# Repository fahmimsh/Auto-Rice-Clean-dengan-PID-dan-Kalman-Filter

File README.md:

# Auto-Rice-Clean-dengan-PID-dan-Kalman-Filter

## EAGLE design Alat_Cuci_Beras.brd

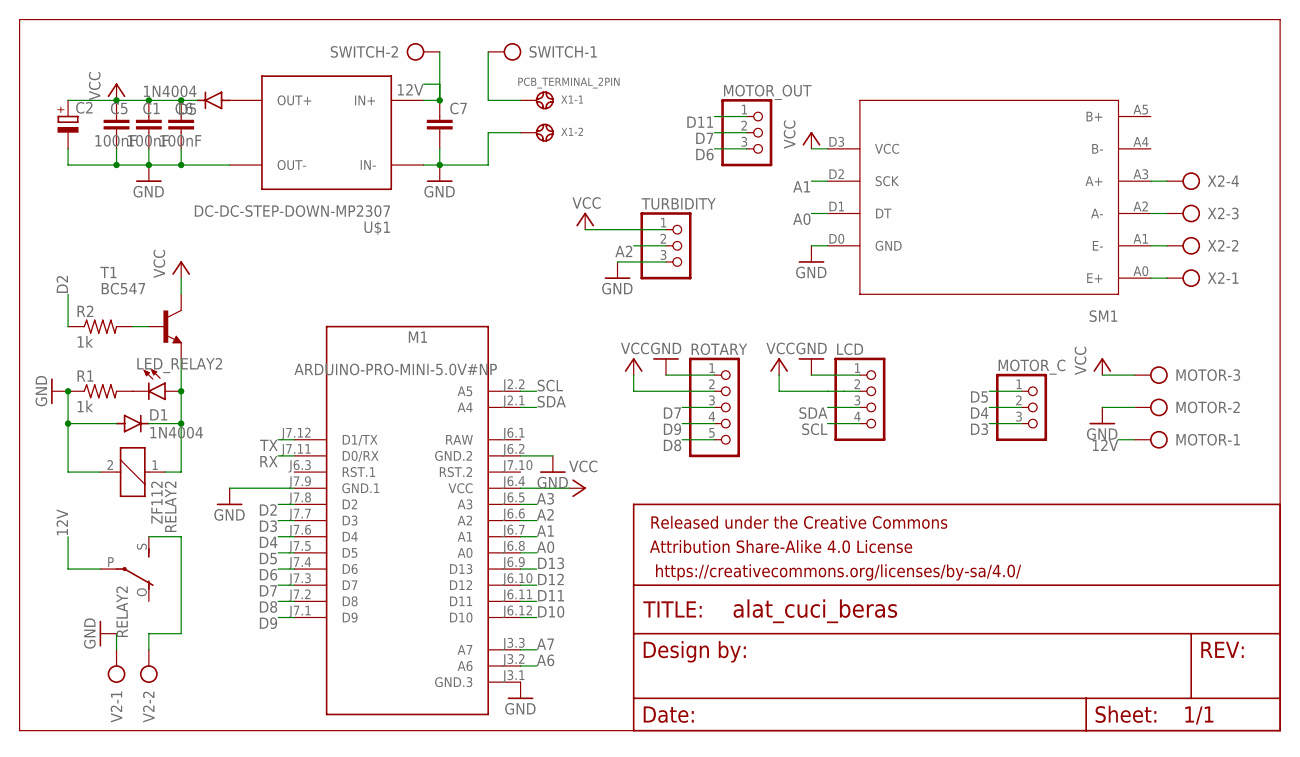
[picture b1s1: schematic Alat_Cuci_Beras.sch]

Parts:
C1, C5, C6: 100nF; C0805K
C2: CPOL-EUE2.5-6; E2,5-6
C7: C-EU050-030X075; C050-030X075
D1, D5: 1N4004; DO41-10
FRAME1: FRAME-LETTER; CREATIVE_COMMONS
LCD: PINHD-1X4; 1X04
LED_RELAY2: LED3MM; LED_3MM
M1: ARDUINO-PRO-MINI-5.0V#NP; ARDUINO-PRO-MINI#NP
MOTOR: AK500/3
MOTOR_C: PINHD-1X3; 1X03
MOTOR_OUT: PINHD-1X3; 1X03
R1: 1k; R0805
R2: 1k; 0207/10
RELAY2: ZF112
ROTARY: PINHD-1X5; 1X05
SM1: HX711
SWITCH: AK500/2
T1: BC547; TO92
TURBIDITY: PINHD-1X3; 1X03
U$1: DC-DC-STEP-DOWN-MP2307
V2: AK500/2
X1: PCB_TERMINAL_2PIN
X2: AK500/4

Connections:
12V: C7.1, MOTOR.1, RELAY2.P, SWITCH.2, U$1.IN+
A0: M1.J6.8 (A0), SM1.D1 (DT)
A1: M1.J6.7 (A1), SM1.D2 (SCK)
A2: M1.J6.6 (A2), TURBIDITY.2
A3: M1.J6.5 (A3)
A6: M1.J3.2 (A6)
A7: M1.J3.3 (A7)
D2: M1.J7.8 (D2), R2.1
D3: M1.J7.7 (D3), MOTOR_C.3
D4: M1.J7.6 (D4), MOTOR_C.2
D5: M1.J7.5 (D5), MOTOR_C.1
D6: M1.J7.4 (D6), MOTOR_OUT.3
D7: M1.J7.3 (D7), MOTOR_OUT.2, ROTARY.3
D8: M1.J7.2 (D8), ROTARY.5
D9: M1.J7.1 (D9), ROTARY.4
D10: M1.J6.12 (D10)
D11: M1.J6.11 (D11), MOTOR_OUT.1
D12: M1.J6.10 (D12)
D13: M1.J6.9 (D13)
GND: C1.2, C2.-, C5.2, C6.2, C7.2, D1.A, LCD.1, M1.J3.1 (GND.3), M1.J6.2 (GND.2), M1.J7.9 (GND.1), MOTOR.2, R1.1, RELAY2.2, ROTARY.1, SM1.D0 (GND), TURBIDITY.3, U$1.IN-, U$1.OUT-, V2.1, X1.2
unnamed: D1.C, LED_RELAY2.A, RELAY2.1, T1.1 (E)
unnamed: SWITCH.1, X1.1
unnamed: D5.A, U$1.OUT+
unnamed: LED_RELAY2.K (C), R1.2
unnamed: R2.2, T1.2 (B)
unnamed: SM1.A0 (E+), X2.1
unnamed: SM1.A1 (E-), X2.2
unnamed: SM1.A2 (A-), X2.3
unnamed: RELAY2.S, V2.2
unnamed: SM1.A3 (A+), X2.4
RAW: M1.J6.1 (RAW)
RX: M1.J7.11 (D0/RX)
SCL: LCD.4, M1.J2.2 (A5)
SDA: LCD.3, M1.J2.1 (A4)
TX: M1.J7.12 (D1/TX)
VCC: C1.1, C2.+, C5.1, C6.1, D5.C, LCD.2, M1.J6.4 (VCC), MOTOR.3, ROTARY.2, SM1.D3 (VCC), T1.3 (C), TURBIDITY.1

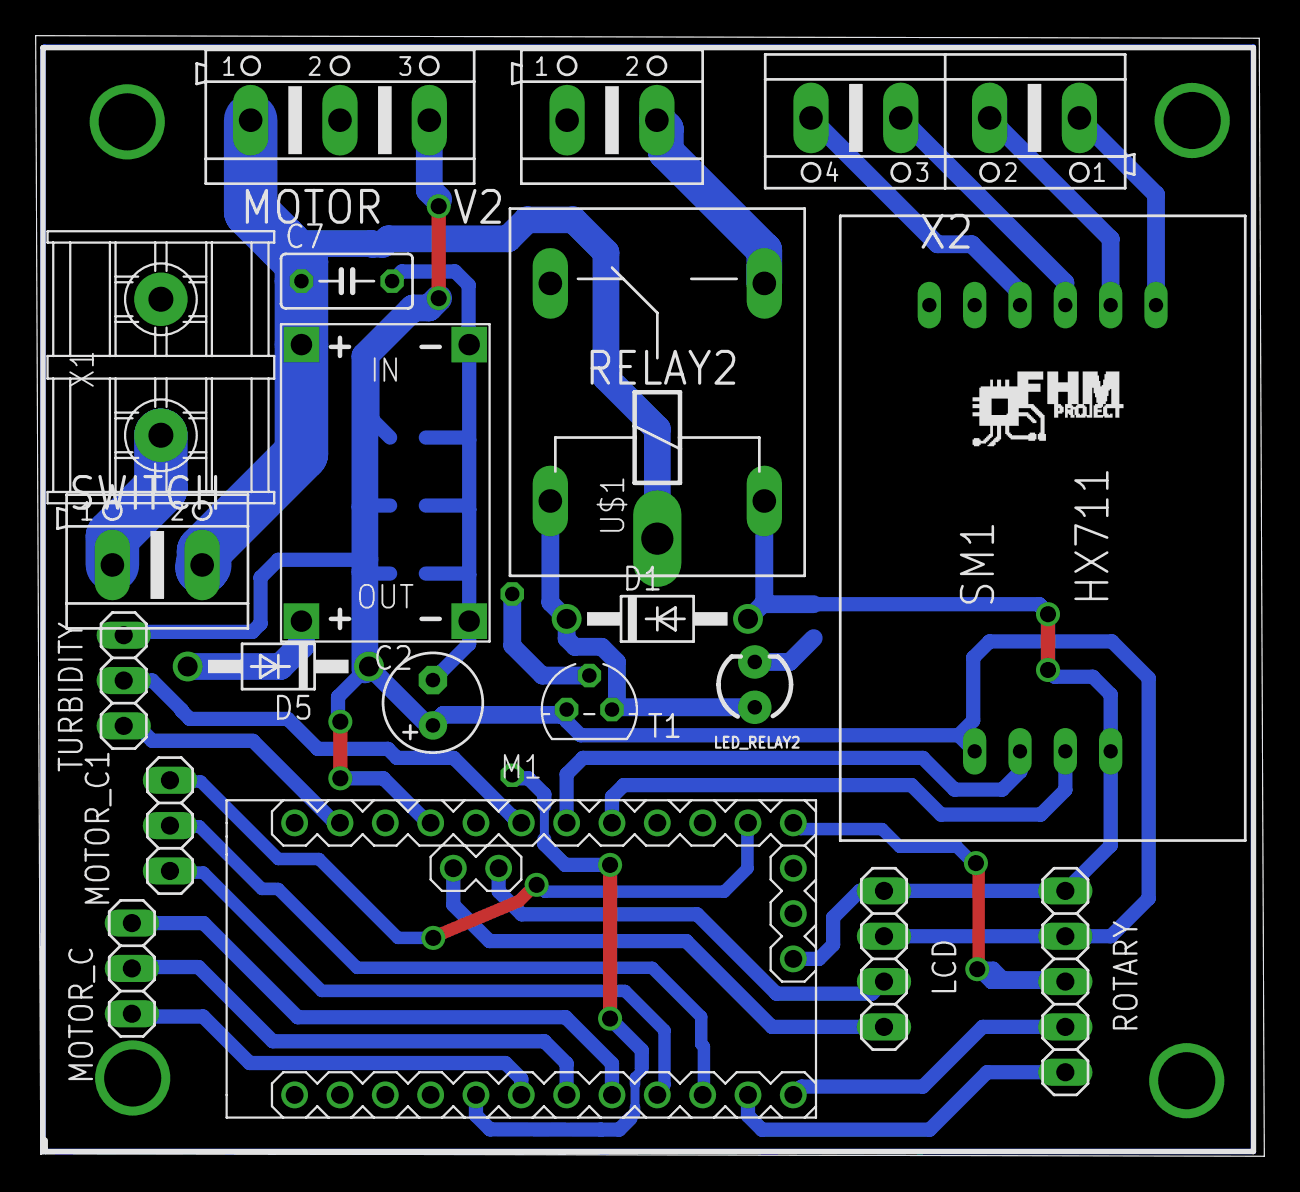
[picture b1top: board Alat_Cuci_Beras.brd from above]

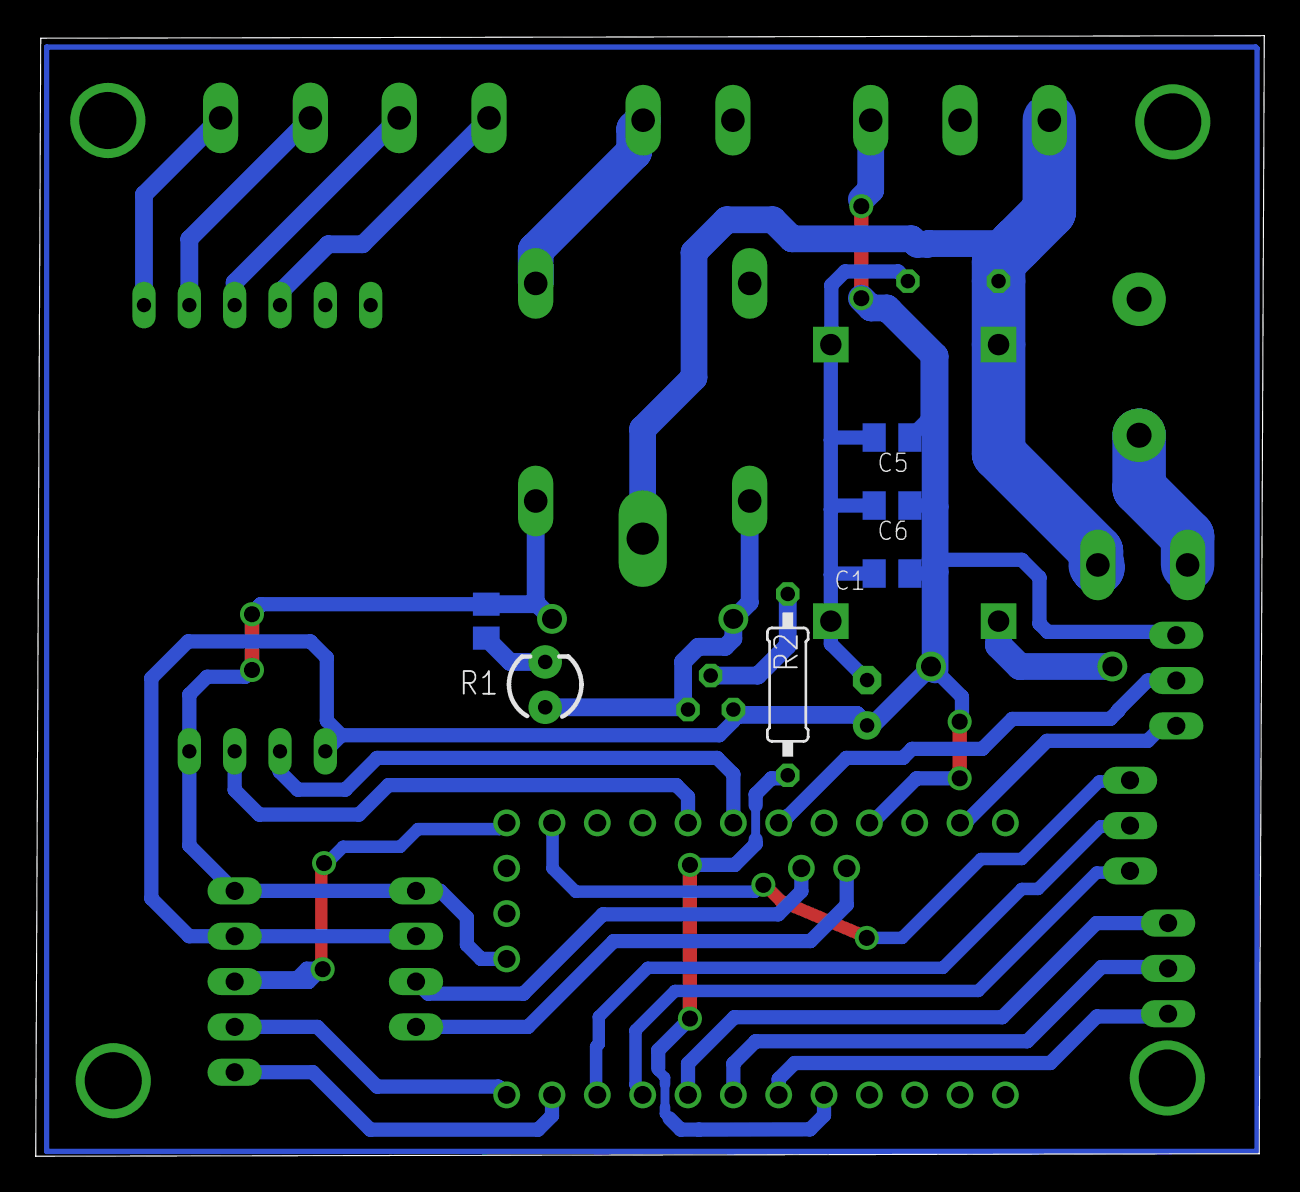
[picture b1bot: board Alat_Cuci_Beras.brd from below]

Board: 2 copper layers, 68.8 x 62.8 mm, 26 parts (5 on the bottom side), 25 nets.

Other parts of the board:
MOTOR_C1: 1X03

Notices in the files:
parts and their libraries:
SparkFun-Aesthetics: Licensing: Creative Commons ShareAlike 4.0 International - https://creativecommons.org/licenses/by-sa/4.0
SparkFun-Aesthetics: Released under the Creative Commons Attribution Share-Alike 4.0 License
SparkFun-Aesthetics: https://creativecommons.org/licenses/by-sa/4.0
